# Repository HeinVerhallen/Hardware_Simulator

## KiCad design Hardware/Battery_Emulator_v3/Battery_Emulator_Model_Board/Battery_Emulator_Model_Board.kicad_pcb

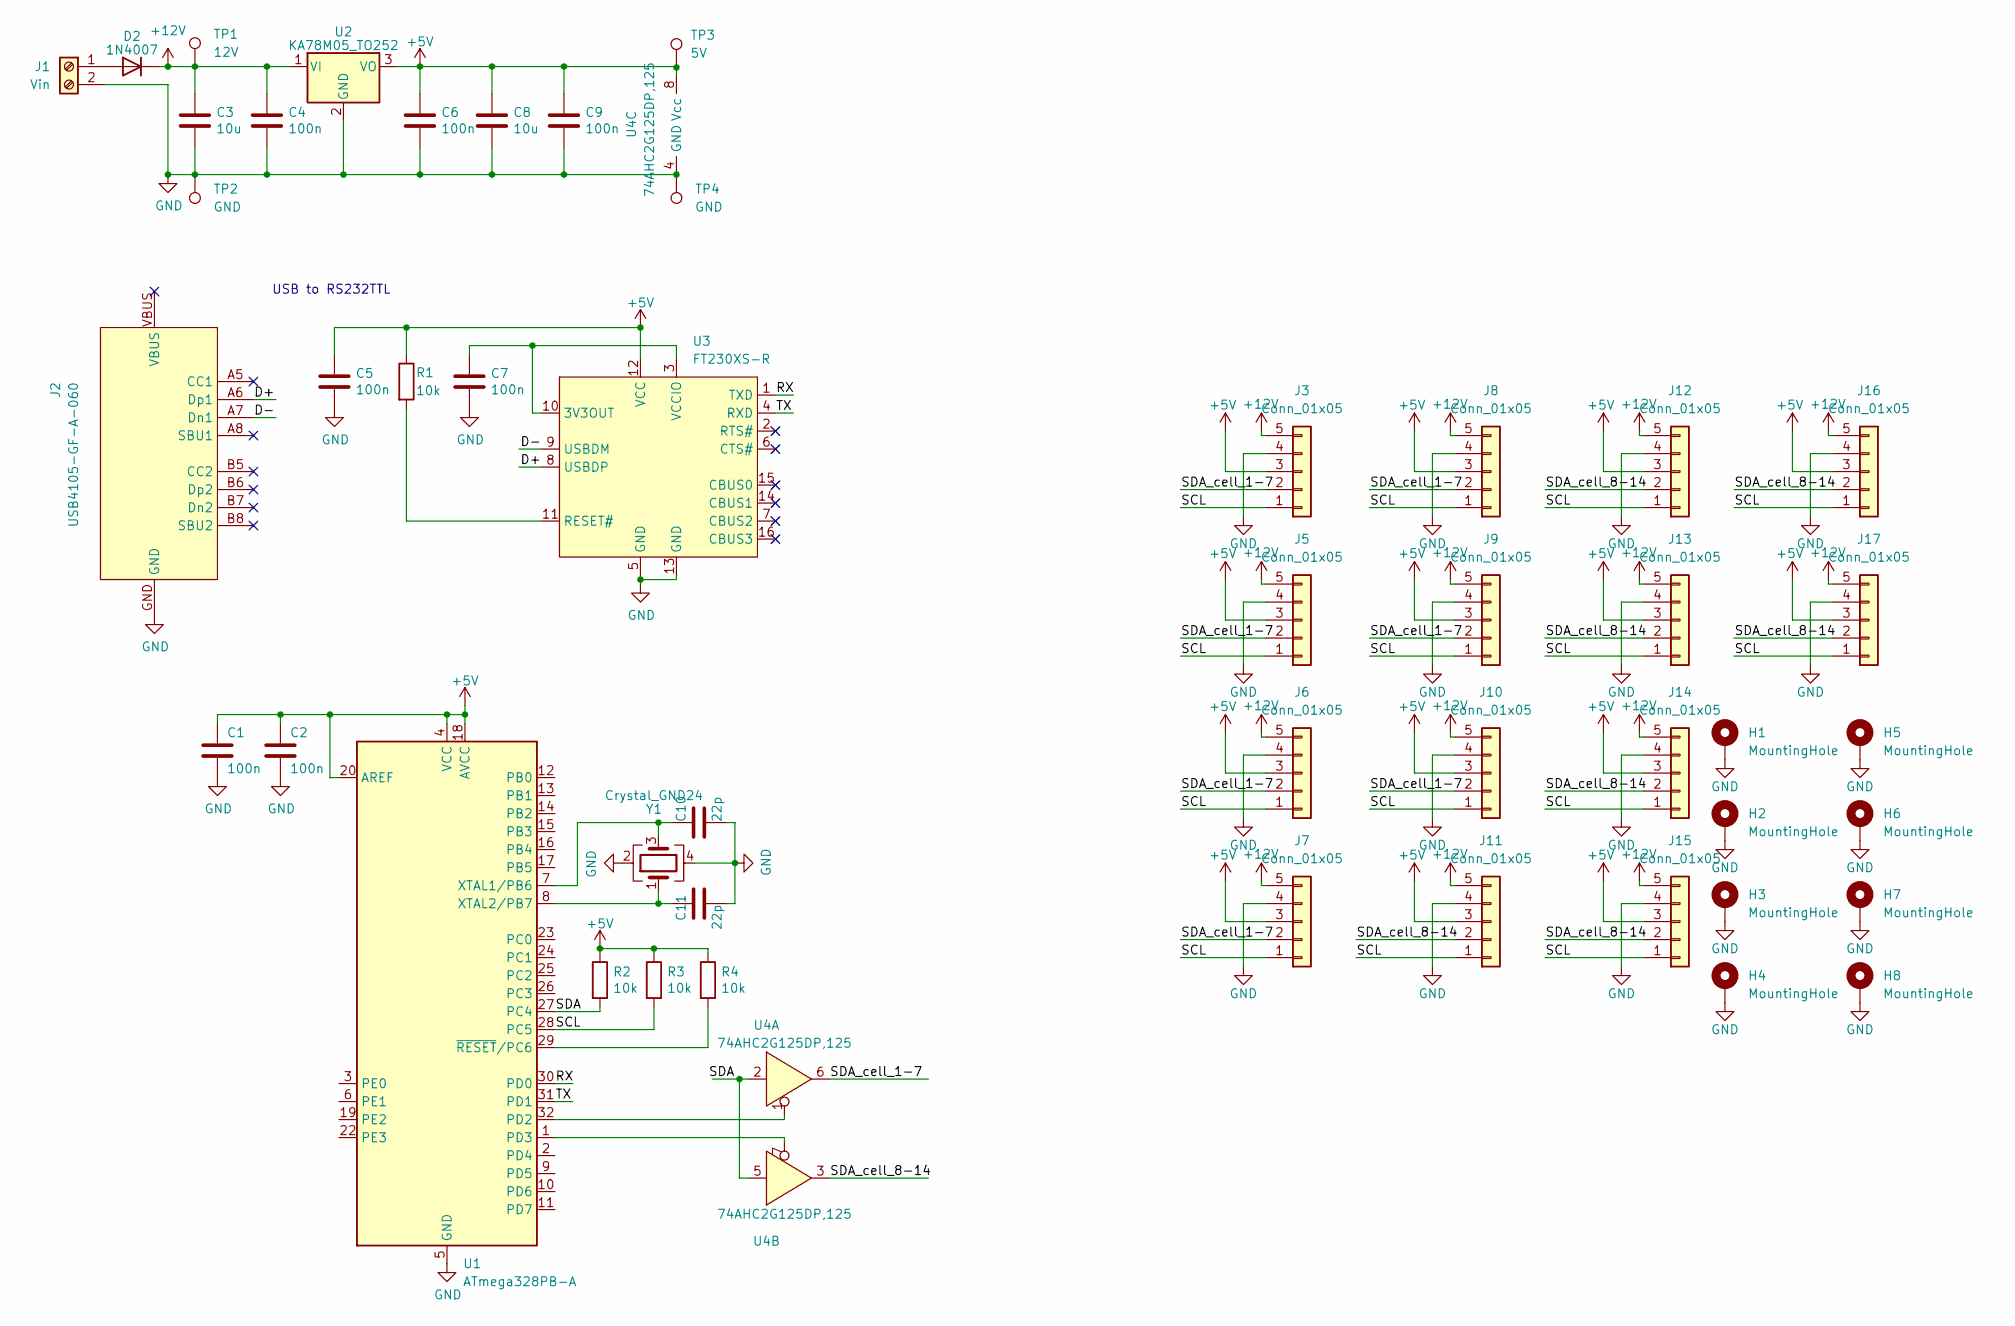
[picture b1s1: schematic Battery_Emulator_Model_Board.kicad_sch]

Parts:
C1, C2, C4, C5, C6, C7, C9: 100n; C_0805_2012Metric
C3, C8: 10u; C_0805_2012Metric
C10, C11: 22p; C_0805_2012Metric
D2: 1N4007; D_DO-41_SOD81_P2.54mm_Vertical_KathodeUp
H1, H2, H3, H4, H5, H6, H7, H8: MountingHole; MountingHole_3.2mm_M3_Pad_Via
J1: Vin; TerminalBlock_Phoenix_MKDS-1,5-2-5.08_1x02_P5.08mm_Horizont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
J2: USB4105-GF-A-060; GCT_USB4105-GF-A-060
J3, J5, J6, J7, J8, J9, J10, J11, J12, J13, J14, J15, J16, J17: Conn_01x05; PinSocket_1x05_P2.54mm_Horizontal
R1, R2, R3, R4: 10k; R_0805_2012Metric
TP1: 12V; TestPoint_Pad_D2.5mm
TP2, TP4: GND; TestPoint_Pad_D2.5mm
TP3: 5V; TestPoint_Pad_D2.5mm
U1: ATmega328PB-A; TQFP-32_7x7mm_P0.8mm
U2: KA78M05_TO252; TO-252-2
U3: FT230XS-R; SSOP-16_3.9x4.9mm_P0.635mm
U4: 74AHC2G125DP,125; TSSOP-8_3x3mm_P0.65mm
Y1: Crystal_GND24; Crystal_SMD_3225-4Pin_3.2x2.5mm

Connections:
+5V: C1.1, C2.1, C5.1, C6.1, C8.1, C9.1, J3.3, J5.3, J6.3, J7.3, J8.3, J9.3, J10.3, J11.3, J12.3, J13.3, J14.3, J15.3, J16.3, J17.3, R1.1, R2.1, R3.1, R4.1, TP3.1, U1.4 (VCC), U1.18 (AVCC), U1.20 (AREF), U2.3 (VO), U3.12 (VCC), U4.8 (Vcc)
+12V: C3.1, C4.1, D2.1 (K), J3.5, J5.5, J6.5, J7.5, J8.5, J9.5, J10.5, J11.5, J12.5, J13.5, J14.5, J15.5, J16.5, J17.5, TP1.1, U2.1 (VI)
/D+: J2.A6 (Dp1), U3.8 (USBDP)
/D-: J2.A7 (Dn1), U3.9 (USBDM)
/RX: U1.30 (PD0), U3.1 (TXD)
/SCL: J3.1, J5.1, J6.1, J7.1, J8.1, J9.1, J10.1, J11.1, J12.1, J13.1, J14.1, J15.1, J16.1, J17.1, R3.2, U1.28 (PC5)
/SDA: R2.2, U1.27 (PC4), U4.2, U4.5
/SDA_cell_1-7: J3.2, J5.2, J6.2, J7.2, J8.2, J9.2, J10.2, U4.6
/SDA_cell_8-14: J11.2, J12.2, J13.2, J14.2, J15.2, J16.2, J17.2, U4.3
/TX: U1.31 (PD1), U3.4 (RXD)
GND: C1.2, C2.2, C3.2, C4.2, C5.2, C6.2, C7.2, C8.2, C9.2, C10.2, C11.2, H1.1, H2.1, H3.1, H4.1, H5.1, H6.1, H7.1, H8.1, J1.2, J2.GND, J3.4, J5.4, J6.4, J7.4, J8.4, J9.4, J10.4, J11.4, J12.4, J13.4, J14.4, J15.4, J16.4, J17.4, TP2.1, TP4.1, U1.5 (GND), U1.21 (GND), U2.2 (GND), U3.5 (GND), U3.13 (GND), U4.4 (GND), Y1.2, Y1.4
unnamed: D2.2 (A), J1.1
unnamed: U1.32 (PD2), U4.1
unnamed: U1.1 (PD3), U4.7
unnamed: C10.1, U1.7 (XTAL1/PB6), Y1.3
unnamed: C11.1, U1.8 (XTAL2/PB7), Y1.1
unnamed: R4.2, U1.29 (~RESET/PC6)
unnamed: C7.1, U3.3 (VCCIO), U3.10 (3V3OUT)
unnamed: R1.2, U3.11 (RESET#)

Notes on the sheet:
USB to RS232TTL

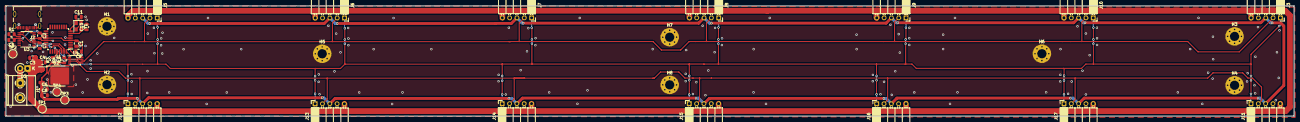
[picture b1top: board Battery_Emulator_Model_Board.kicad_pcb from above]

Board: 2 copper layers, 446.7 x 38.2 mm, 49 parts (0 on the bottom side), 19 nets.

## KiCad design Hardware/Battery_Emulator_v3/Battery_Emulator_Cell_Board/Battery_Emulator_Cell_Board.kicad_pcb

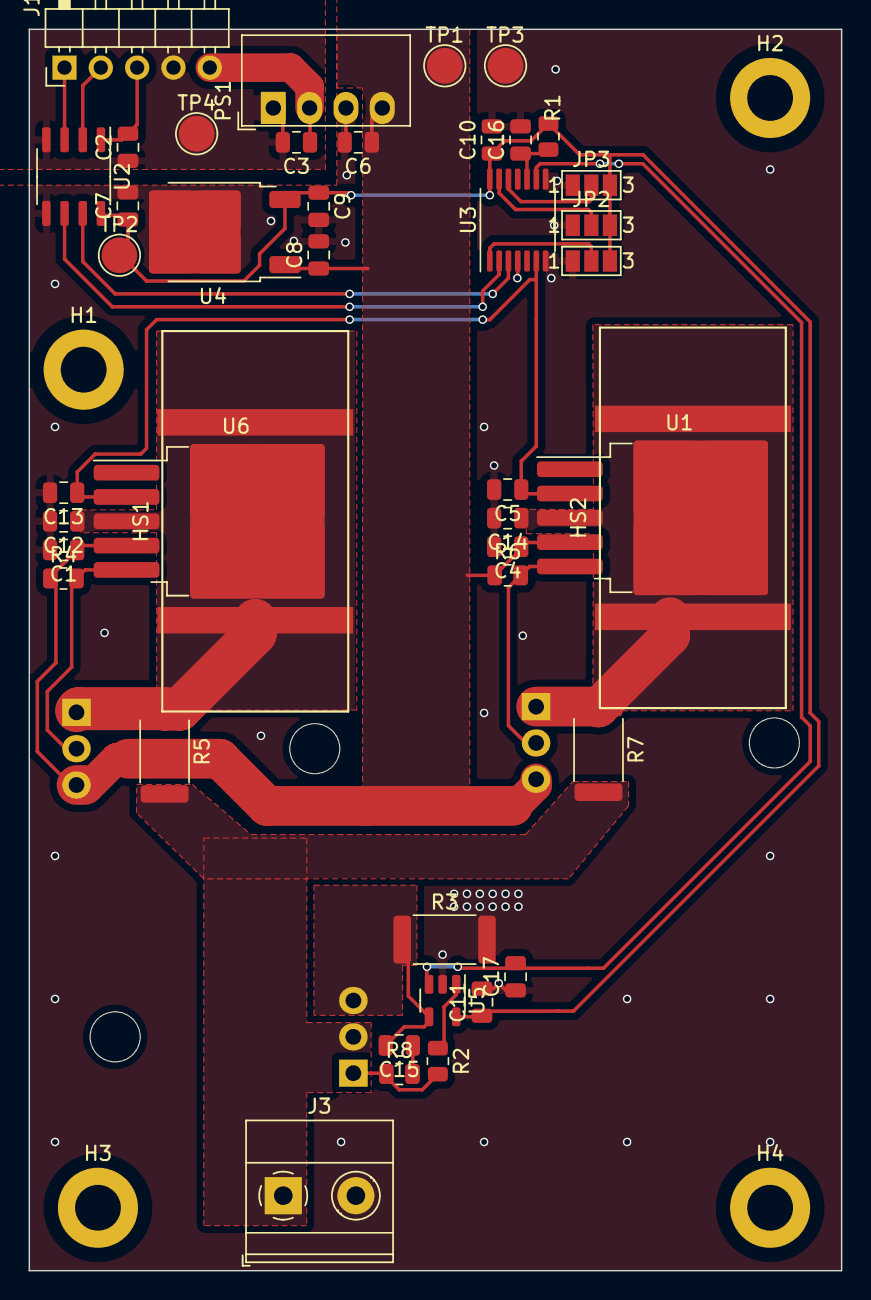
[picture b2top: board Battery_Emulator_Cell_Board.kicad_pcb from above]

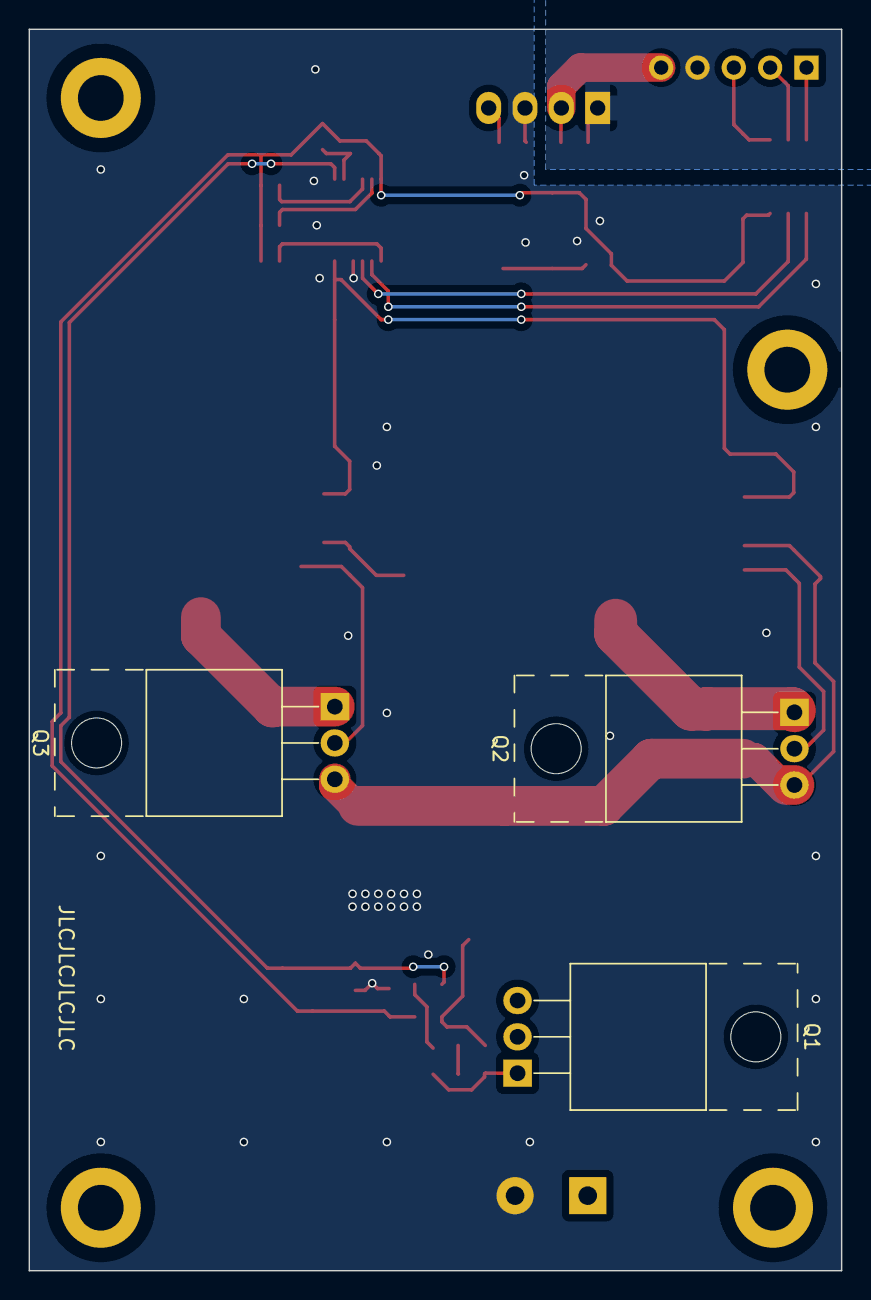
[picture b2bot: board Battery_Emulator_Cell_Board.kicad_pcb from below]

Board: 2 copper layers, 56.8 x 86.8 mm, 50 parts (3 on the bottom side), 25 nets.

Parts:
C1, C4: 1u; C_0805_2012Metric
C2, C7, C8, C9, C10, C11, C16: 100n; C_0805_2012Metric
C3, C6: 10u; C_0805_2012Metric
C5, C13: 1n; C_0805_2012Metric
C12, C14: 2u2; C_0805_2012Metric
C15: 330n; C_0805_2012Metric
C17: 10n; C_0805_2012Metric
H1, H2, H3, H4: MountingHole; MountingHole_3.2mm_M3_DIN965_Pad
HS1, HS2: Heatsink_Pad_2Pin; Heatsink_AAVID_573300D00010G_TO-263
J1: Conn_01x05; PinHeader_1x05_P2.54mm_Horizontal
J3: Cell1_Vout; TerminalBlock_Phoenix_MKDS-1,5-2-5.08_1x02_P5.08mm_Horizont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
JP1, JP2, JP3: Jumper; SolderJumper-3_P1.3mm_Open_Pad1.0x1.5mm_NumberLabels
PS1: MEE1S1209SC; Converter_DCDC_Murata_MEE1SxxxxSC_THT
Q1: IRFB7545PBF; TO-220-3_Horizontal_TabUp
Q2, Q3: MJE2955T; TO-220-3_Horizontal_TabUp
R1: 780k; R_0805_2012Metric
R2: 10k; R_0805_2012Metric
R3: 0.5m; R_2512_6332Metric
R4, R6: 47; R_0805_2012Metric
R5, R7: 20m; R_2512_6332Metric
R8: 56; R_0805_2012Metric
TP1: 9V_ISO; TestPoint_Pad_D2.5mm
TP2: 5V_ISO; TestPoint_Pad_D2.5mm
TP3: GND_ISO; TestPoint_Pad_D2.5mm
TP4: GND; TestPoint_Pad_D2.5mm
U1, U6: LT3080xQ; TO-263-5_TabPin3
U2: ISO1640BDR; SO-8_3.9x4.9mm_P1.27mm
U3: MCP4651T-103E_ST; TSSOP-14_4.4x5mm_P0.65mm
U4: KA78M05_TO252; TO-252-2
U5: MCP6001UT-I/OT; SOT-23-5

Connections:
/+5V: C2.2, J1.3, U2.1 (VCC1)
/+5V_ISO: C7.1, C9.1, C10.1, C11.1, JP1.3 (B), JP2.3 (B), JP3.3 (B), R1.1, TP2.1, U2.8 (VCC2), U3.14 (VDD), U4.3 (VO), U5.5 (Vdd)
/+9V_ISO: C1.1, C4.1, C6.1, C8.1, PS1.4 (+Vout), Q2.3 (E), Q3.3 (E), R4.1, R6.1, TP1.1, U1.4 (VCONTROL), U4.1 (VI), U6.4 (VCONTROL)
/+12V: C3.1, J1.5, PS1.2 (+Vin)
/A0: JP1.2 (C), U3.1 (HVC/A0)
/A1: JP2.2 (C), U3.13 (A1)
/A2: JP3.2 (C), U3.12 (A2)
/GND: C2.1, C3.2, J1.4, PS1.1 (-Vin), TP4.1, U2.4 (GND1)
/GND_ISO: C1.2, C4.2, C5.2, C6.2, C7.2, C8.2, C9.2, C10.2, C11.2, C12.2, C13.2, C14.2, C16.2, C17.1, J3.2, JP1.1 (A), JP2.1 (A), JP3.1 (A), PS1.3 (-Vout), R3.2, TP3.1, U2.5 (GND2), U3.4 (VSS), U3.7 (P1A), U3.8 (P0A), U4.2 (GND), U5.2 (Vss)
/I_sense: C15.2, Q1.3, R3.1, U5.4 (-)
/OUT1_ISO: C14.1, HS2.1, Q3.1 (C), R7.1, U1.3 (OUT)
/OUT2_ISO: C12.1, HS1.1, Q2.1 (C), R5.1, U6.3 (OUT)
/SCL: J1.1, U2.3 (SCL1)
/SCL_ISO: U2.6 (SCL2), U3.2 (SCL)
/SDA: J1.2, U2.2 (SDA1)
/SDA_ISO: U2.7 (SDA2), U3.3 (SDA)
unnamed: C15.1, R8.2
unnamed: J3.1, Q1.2, R5.2, R7.2
unnamed: Q1.1, R2.2, R8.1
unnamed: Q2.2 (B), R4.2, U6.5 (IN)
unnamed: Q3.2 (B), R6.2, U1.5 (IN)
unnamed: R2.1, U5.1
unnamed: C5.1, C13.1, U1.2 (SET), U3.6 (P1W), U6.2 (SET)
unnamed: C16.1, R1.2, U3.10 (P0B)
unnamed: C17.2, U3.9 (P0W), U5.3 (+)

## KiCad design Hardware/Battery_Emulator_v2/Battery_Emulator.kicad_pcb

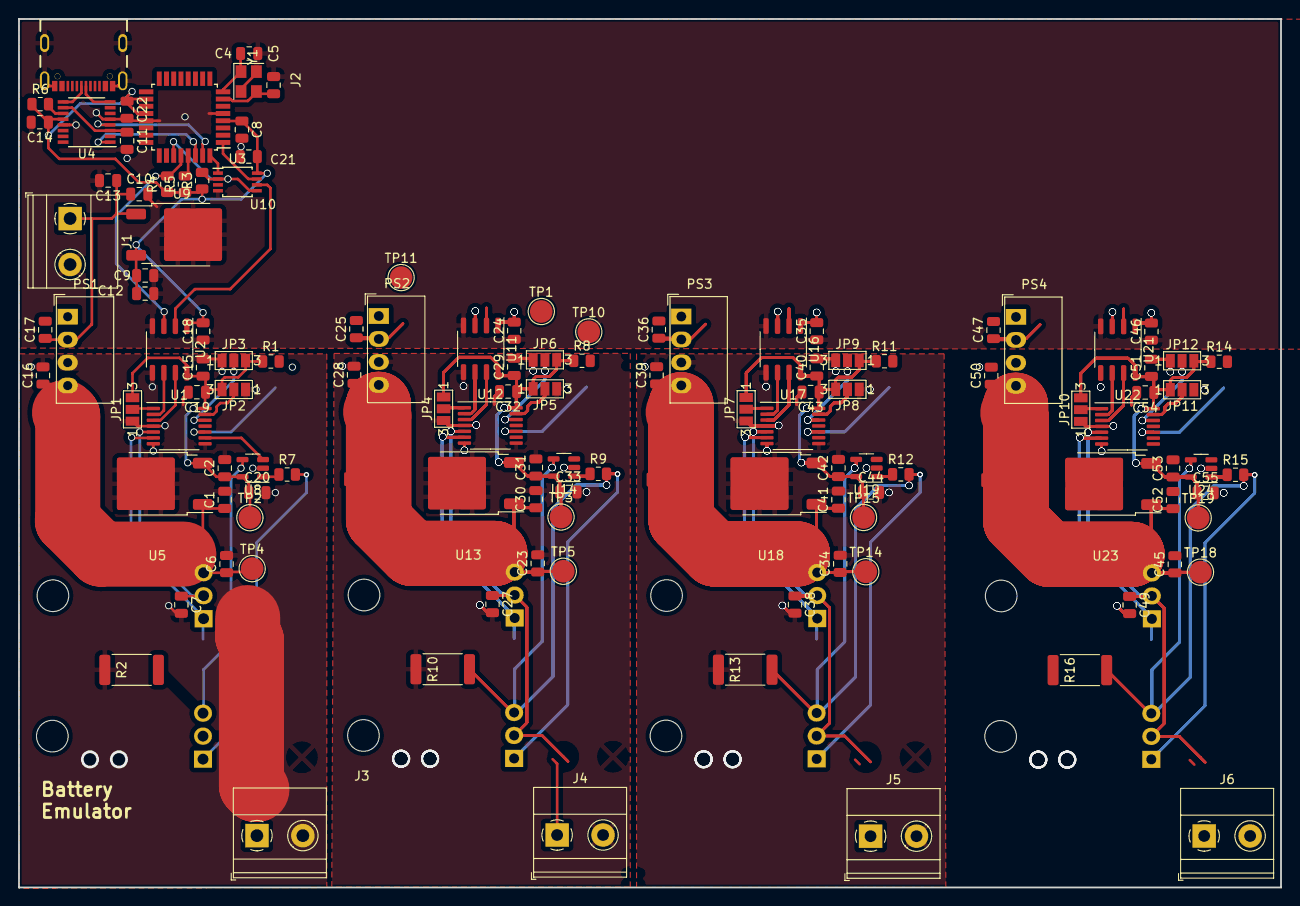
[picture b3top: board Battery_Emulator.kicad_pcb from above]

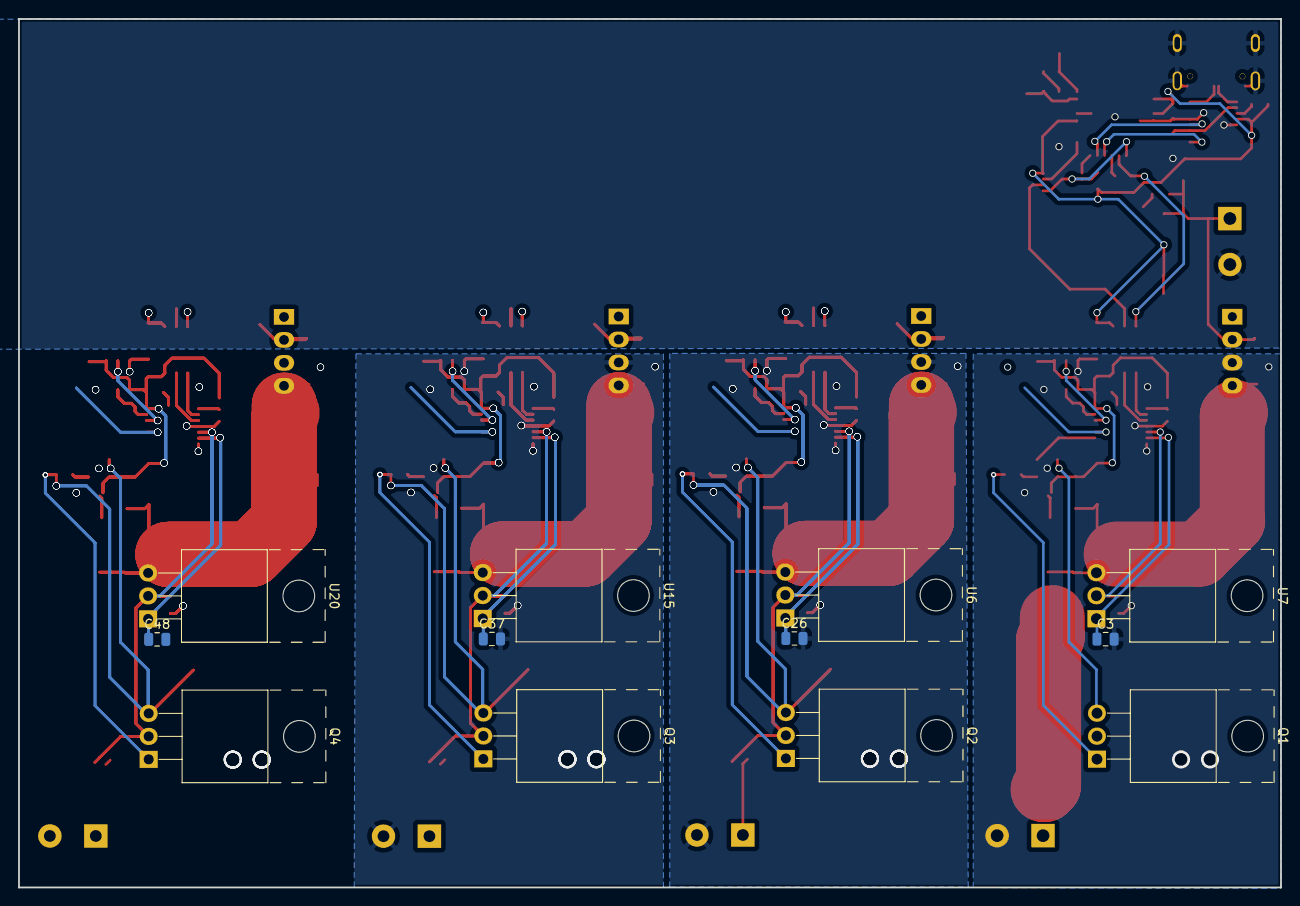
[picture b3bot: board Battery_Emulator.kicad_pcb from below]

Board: 2 copper layers, 139.5 x 96.0 mm, 133 parts (12 on the bottom side), 80 nets.

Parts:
C1, C2, C3, C6, C7, C8, C9, C10, C11, C14, C15, C18, C19, C20, C21, C22, C23, C24, C26, C27, C29, C30, C31, C32, C33, C34, C35, C37, C38, C40, C41, C42, C43, C44, C45, C46, C48, C49, C51, C52, C53, C54, C55: 100n; C_0805_2012Metric
C4, C5: 22p; C_0805_2012Metric
C12, C13, C16, C17, C25, C28, C36, C39, C47, C50: 10u; C_0805_2012Metric
J1: Vin; TerminalBlock_Phoenix_MKDS-1,5-2-5.08_1x02_P5.08mm_Horizont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
J2: USB4105-GF-A-060; GCT_USB4105-GF-A-060
J3: Cell1_Vout; TerminalBlock_Phoenix_MKDS-1,5-2-5.08_1x02_P5.08mm_Horizont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
J4: Cell2_Vout; TerminalBlock_Phoenix_MKDS-1,5-2-5.08_1x02_P5.08mm_Horizont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
J5: Cell3_Vout; TerminalBlock_Phoenix_MKDS-1,5-2-5.08_1x02_P5.08mm_Horizont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
J6: Cell4_Vout; TerminalBlock_Phoenix_MKDS-1,5-2-5.08_1x02_P5.08mm_Horizont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
JP1, JP2, JP3, JP4, JP5, JP6, JP7, JP8, JP9, JP10, JP11, JP12: Jumper; SolderJumper-3_P1.3mm_Open_Pad1.0x1.5mm_NumberLabels
PS1, PS2, PS3, PS4: MEE1S1209SC; Converter_DCDC_Murata_MEE1SxxxxSC_THT
Q1, Q2, Q3, Q4: IRFB7545PBF; TO-220-3_Horizontal_TabUp
R1, R8, R11, R14: 780k; R_0805_2012Metric
R2, R10, R13, R16: 0.5m; R_2512_6332Metric
R3, R4, R5, R6: 10k; R_0805_2012Metric
R7, R9, R12, R15: 47; R_0805_2012Metric
TP1: 5V; TestPoint_Pad_D2.5mm
TP2, TP3, TP15, TP19: 5V_ISO; TestPoint_Pad_D2.5mm
TP4, TP5, TP14, TP18: 9V_ISO; TestPoint_Pad_D2.5mm
TP10: GND; TestPoint_Pad_D2.5mm
TP11: 12V; TestPoint_Pad_D2.5mm
U1, U12, U17, U22: MCP4651T-103E_ST; TSSOP-14_4.4x5mm_P0.65mm
U2, U11, U16, U21: ISO1640BDR; SO-8_3.9x4.9mm_P1.27mm
U3: 74AHC2G125DP,125; TSSOP-8_3x3mm_P0.65mm
U4: FT230XS-R; SSOP-16_3.9x4.9mm_P0.635mm
U5, U9, U13, U18, U23: KA78M05_TO252; TO-252-2
U6, U7, U15, U20: LM317_TO-220; TO-220-3_Horizontal_TabUp
U8, U14, U19, U24: MCP6001UT-I/OT; SOT-23-5
U10: ATmega328PB-A; TQFP-32_7x7mm_P0.8mm
Y1: Crystal_GND24; Crystal_SMD_3225-4Pin_3.2x2.5mm

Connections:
+5V: C8.1, C9.1, C12.1, C14.1, C18.2, C21.1, C22.1, C24.2, C35.2, C46.2, R3.1, R4.1, R5.1, R6.1, TP1.1, U2.1 (VCC1), U3.8 (Vcc), U4.12 (VCC), U9.3 (VO), U10.4 (VCC), U10.18 (AVCC), U10.20 (AREF), U11.1 (VCC1), U16.1 (VCC1), U21.1 (VCC1)
+12V: C10.1, C13.1, C17.1, C25.1, C36.1, C47.1, J1.1, PS1.2 (+Vin), PS2.2 (+Vin), PS3.2 (+Vin), PS4.2 (+Vin), TP11.1, U9.1 (VI)
/Cell_1/+5V_ISO: C2.1, C15.1, C19.1, C20.1, JP1.3 (B), JP2.3 (B), JP3.3 (B), R1.1, TP2.1, U1.14 (VDD), U2.8 (VCC2), U5.3 (VO), U8.5 (Vdd)
/Cell_1/+9V_ISO: C1.1, C6.1, C16.1, PS1.4 (+Vout), TP4.1, U5.1 (VI), U7.3 (VI)
/Cell_1/A0: JP1.2 (C), U1.1 (HVC/A0)
/Cell_1/A1: JP2.2 (C), U1.13 (A1)
/Cell_1/A2: JP3.2 (C), U1.12 (A2)
/Cell_1/GND_ISO: C1.2, C2.2, C3.2, C6.2, C7.2, C15.2, C16.2, C19.2, C20.2, J3.2, JP1.1 (A), JP2.1 (A), JP3.1 (A), PS1.3 (-Vout), R2.2, U1.4 (VSS), U1.7 (P1A), U1.8 (P0A), U2.5 (GND2), U5.2 (GND), U8.2 (Vss)
/Cell_1/SCL_ISO: U1.2 (SCL), U2.6 (SCL2)
/Cell_1/SDA_ISO: U1.3 (SDA), U2.7 (SDA2)
/Cell_2/+5V_ISO: C29.1, C31.1, C32.1, C33.1, JP4.3 (B), JP5.3 (B), JP6.3 (B), R8.1, TP3.1, U11.8 (VCC2), U12.14 (VDD), U13.3 (VO), U14.5 (Vdd)
/Cell_2/+9V_ISO: C23.1, C28.1, C30.1, PS2.4 (+Vout), TP5.1, U6.3 (VI), U13.1 (VI)
/Cell_2/A0: JP4.2 (C), U12.1 (HVC/A0)
/Cell_2/A1: JP5.2 (C), U12.13 (A1)
/Cell_2/A2: JP6.2 (C), U12.12 (A2)
/Cell_2/COUT+: C27.1, J4.1, Q2.2, U6.2 (VO), U12.5 (P1B)
/Cell_2/GND_ISO: C23.2, C26.2, C27.2, C28.2, C29.2, C30.2, C31.2, C32.2, C33.2, J4.2, JP4.1 (A), JP5.1 (A), JP6.1 (A), PS2.3 (-Vout), R10.2, U11.5 (GND2), U12.4 (VSS), U12.7 (P1A), U12.8 (P0A), U13.2 (GND), U14.2 (Vss)
/Cell_2/SCL_ISO: U11.6 (SCL2), U12.2 (SCL)
/Cell_2/SDA_ISO: U11.7 (SDA2), U12.3 (SDA)
/Cell_3/+5V_ISO: C40.1, C42.1, C43.1, C44.1, JP7.3 (B), JP8.3 (B), JP9.3 (B), R11.1, TP15.1, U16.8 (VCC2), U17.14 (VDD), U18.3 (VO), U19.5 (Vdd)
/Cell_3/+9V_ISO: C34.1, C39.1, C41.1, PS3.4 (+Vout), TP14.1, U15.3 (VI), U18.1 (VI)
/Cell_3/A0: JP7.2 (C), U17.1 (HVC/A0)
/Cell_3/A1: JP8.2 (C), U17.13 (A1)
/Cell_3/A2: JP9.2 (C), U17.12 (A2)
/Cell_3/COUT+: C38.1, J5.1, Q3.2, U15.2 (VO), U17.5 (P1B)
/Cell_3/GND_ISO: C34.2, C37.2, C38.2, C39.2, C40.2, C41.2, C42.2, C43.2, C44.2, J5.2, JP7.1 (A), JP8.1 (A), JP9.1 (A), PS3.3 (-Vout), R13.2, U16.5 (GND2), U17.4 (VSS), U17.7 (P1A), U17.8 (P0A), U18.2 (GND), U19.2 (Vss)
/Cell_3/SCL_ISO: U16.6 (SCL2), U17.2 (SCL)
/Cell_3/SDA_ISO: U16.7 (SDA2), U17.3 (SDA)
/Cell_4/+5V_ISO: C51.1, C53.1, C54.1, C55.1, JP10.3 (B), JP11.3 (B), JP12.3 (B), R14.1, TP19.1, U21.8 (VCC2), U22.14 (VDD), U23.3 (VO), U24.5 (Vdd)
/Cell_4/+9V_ISO: C45.1, C50.1, C52.1, PS4.4 (+Vout), TP18.1, U20.3 (VI), U23.1 (VI)
/Cell_4/A0: JP10.2 (C), U22.1 (HVC/A0)
/Cell_4/A1: JP11.2 (C), U22.13 (A1)
/Cell_4/A2: JP12.2 (C), U22.12 (A2)
/Cell_4/COUT+: C49.1, J6.1, Q4.2, U20.2 (VO), U22.5 (P1B)
/Cell_4/GND_ISO: C45.2, C48.2, C49.2, C50.2, C51.2, C52.2, C53.2, C54.2, C55.2, J6.2, JP10.1 (A), JP11.1 (A), JP12.1 (A), PS4.3 (-Vout), R16.2, U21.5 (GND2), U22.4 (VSS), U22.7 (P1A), U22.8 (P0A), U23.2 (GND), U24.2 (Vss)
/Cell_4/SCL_ISO: U21.6 (SCL2), U22.2 (SCL)
/Cell_4/SDA_ISO: U21.7 (SDA2), U22.3 (SDA)
/D+: J2.A6 (Dp1), U4.8 (USBDP)
/D-: J2.A7 (Dn1), U4.9 (USBDM)
/RX: U4.1 (TXD), U10.30 (PD0)
/SCL: R4.2, U2.3 (SCL1), U10.28 (PC5), U11.3 (SCL1), U16.3 (SCL1), U21.3 (SCL1)
/SDA: R3.2, U3.2, U3.5, U10.27 (PC4)
/SDA_cell_1-7: U2.2 (SDA1), U3.6, U11.2 (SDA1), U16.2 (SDA1), U21.2 (SDA1)
/TX: U4.4 (RXD), U10.31 (PD1)
GND: C4.2, C5.2, C8.2, C9.2, C10.2, C11.2, C12.2, C13.2, C14.2, C18.1, C21.2, C22.2, C24.1, C35.1, C46.1, J1.2, J2.GND, TP10.1, U2.4 (GND1), U3.4 (GND), U4.5 (GND), U4.13 (GND), U9.2 (GND), U10.5 (GND), U10.21 (GND), U11.4 (GND1), U16.4 (GND1), U21.4 (GND1), Y1.2, Y1.4
unnamed: C17.2, PS1.1 (-Vin)
unnamed: C25.2, PS2.1 (-Vin)
unnamed: C36.2, PS3.1 (-Vin)
unnamed: C47.2, PS4.1 (-Vin)
unnamed: Q1.1, R7.2
unnamed: Q2.1, R9.2
unnamed: Q3.1, R12.2
unnamed: Q4.1, R15.2
unnamed: R7.1, U8.1
unnamed: R9.1, U14.1
unnamed: R12.1, U19.1
unnamed: R15.1, U24.1
unnamed: R1.2, U1.10 (P0B)
unnamed: U1.9 (P0W), U8.3 (+)
unnamed: C3.1, U1.6 (P1W), U7.1 (ADJ)
unnamed: C11.1, U4.3 (VCCIO), U4.10 (3V3OUT)
unnamed: R6.2, U4.11 (RESET#)
unnamed: C7.1, J3.1, Q1.2, Q1.3, R2.1, U1.5 (P1B), U7.2 (VO), U8.4 (-)
unnamed: U3.1, U10.32 (PD2)
unnamed: U3.7, U10.1 (PD3)
unnamed: C5.1, U10.7 (XTAL1/PB6), Y1.3
unnamed: C4.1, U10.8 (XTAL2/PB7), Y1.1
unnamed: R5.2, U10.29 (~RESET/PC6)
unnamed: R8.2, U12.10 (P0B)
unnamed: U12.9 (P0W), U14.3 (+)
unnamed: C26.1, U6.1 (ADJ), U12.6 (P1W)
unnamed: Q2.3, R10.1, U14.4 (-)
unnamed: C37.1, U15.1 (ADJ), U17.6 (P1W)
unnamed: R11.2, U17.10 (P0B)
unnamed: U17.9 (P0W), U19.3 (+)
unnamed: Q3.3, R13.1, U19.4 (-)
unnamed: C48.1, U20.1 (ADJ), U22.6 (P1W)
unnamed: R14.2, U22.10 (P0B)
unnamed: U22.9 (P0W), U24.3 (+)
unnamed: Q4.3, R16.1, U24.4 (-)

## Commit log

2023-09-04 Created Plan of approach Latex doc
2023-09-05 Update PoA
    Added abbreviations in main.tex
2023-09-05 Added block diagram of project description
2023-09-05 Update PoA
    Added text to project result chapter
2023-09-05 Update PoA
    Updated global project description diagram.
    Updated text in projectresult chapter.
2023-09-05 Update PoA
    updated project result
2023-09-05 Riskanalysis
2023-09-05 quality assurance
2023-09-05 Background added
2023-09-05 Updated Background
    removed align and added new lines
2023-09-05 updated QA
2023-09-05 Updates PoA
2023-09-05 Added Milestones
2023-09-05 Added cost benefit
2023-09-05 Update Background.tex
    Replaced the \\ with normal enters which doesn't change the layout.
2023-09-05 Updated Projectboundaries.tex
2023-09-05 Update PoA
    Added planning in planning chapter and made it a landscape page such that the planning fits.
    Also created a new detailed planning in excel.
2023-09-05 Update main.tex
    Updated abbreviation list
2023-09-08 Update PoA
    processed feedback we got from Ralph. Fixed requirements, added mid-term presentation in planning. Added reference to table in risk analysis. Adjusted sentence in project boundaries.
2023-09-08 Small change in cost-benefit
    Changed "you" to "the team"
2023-09-08 Added team meetings
2023-09-08 layout edit
2023-09-13 Updated project organization and risk analysis
2023-09-13 updated projectboundaries
2023-09-13 Updated Milestones
2023-09-13 Update PoA
    added new part in project result chapter.
    Made functional and non-functional requirements in excel document.
2023-09-13 Made a simple simulation of the operating principle of a DC-load
2023-09-19 Created updated broad planning
2023-09-20 Update PoA
2023-09-20 Update PoA
    Updated broad planning. Included requirements and broad planning in latex as image
2023-09-20 Cleaned up PoA
2023-09-20 Changed file structure in Documentation folder
2023-09-20 added commas, added 4th iteration in project activities
2023-09-27 Update broad planning
2023-09-27 Made pictures from battery cell diagram
2023-10-04 Created Battery Emulator Schematic
2023-10-04 DC-motor updates
2023-10-04 configured custom symbols and footprints structure
2023-10-04 deleted old kicad version files
2023-10-04 migrated the symbol library
2023-10-04 Created current sink simulation
2023-10-04 Added Cell Hierachy
2023-10-04 Added FT230XS-R
2023-10-11 Added USB-C and Crystal Components
    Symbols + Footprints
2023-10-11 Created avr-i2c-library
2023-10-11 Added ATMega and fixed isolated voltage level
    12V_ISO -> 9V_ISO
2023-10-11 Created cell_emulator code
2023-10-11 Inputted all components and values
2023-10-11 small move of a gnd
2023-10-25 Updated schematic battery emulator
    Made schematic more clear. Fixed some bugs
2023-10-25 wrote code for voltage level setting
2023-11-01 Added components to PCB and started the layout
    Also added footprints for the pots, jumpers and power connector
2023-11-01 Update PCB
    Made PCB in Kicad
2023-11-01 Update PCB design
2023-11-01 Worked on current sink simulations in order to improve stability
2023-11-01 Update PCB
    Made traces a lot larger to pass more current.
    Added resistor to gate of current sink MOSFET.
    Made the gerber files and ordered it at SMD lab.
2023-11-02 Update PCB
    Changed via hole sizes to 0.6mm so it can be made in SMD lab
2023-11-06 Added a second version of the hardware
2023-11-06 Modified the v2 pcb
2023-11-06 Update PCB
    Updated the via sizes to 0.8mm in v1
2023-11-07 PCB-update for production
2023-11-15 testplan
2023-11-15 Hardware Update
    V2 with four cells with the same layout
2023-11-15 Linear regulator simulations addidions and cleanup
2023-11-15 Hardware Update
    Made a v3 that has a model board PCB and a cell board PCB. Made both schematics and started on the layout of the model board PCB.
2023-11-22 Hardware Update
    Updated the v3 model board PCB layout.
2023-11-22 Hardware Update
    Finished the Model Board PCB
2023-11-22 added ESR resistance for stabililty
2023-11-22 Hardware update
    updated the model board pcb and the cell pcb
2023-11-22 Added new lin-reg topology. Use this LT3080-1 schematic for the design
2023-11-22 Update battery emulator v3 design
    Updated design such that its is parallel with the pins
2023-11-23 Updated mother board + cell PCB
    Made +12V trace on mother board 2mm so it can withstand 2A. Improved routing a bit. Changed pinheader to pinsocket on motherboard and pinsocket to pinheader on cell PCB. Mother board is nearly finish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
2023-11-27 Updated model board a bit after review
2023-11-29 Updated Mother board and Cell board
    Changed pinout of mother board and cell board such that the pin headers are on the top side. Finished mother board PCB and did DRC check on it.
2023-11-29 Updated Lin reg simulation to LT3080 instead of LT3080-1
2023-11-29 Hardware Update
    Added the symbols for the LT3080, and the transistor
2023-11-29 added current sink control
2023-11-29 added reverse polarity protection
2023-11-29 Update Cell emulator PCB
2023-11-29 Hardware Update
    Updated the layout of the cell board PCB
2023-11-29 added diode
2023-11-29 added current sink resistor
2023-12-06 update schematic
2023-12-06 Hardware update
    Updated the size of the model board, so that it has 65mm of space for each cell board.
2023-12-06 Hardware update
    Moved some of the ground vias
2023-12-06 Update Cell board
    Finished PCB layout design.
    Added two capacitors in schematic for stable feedback network for current sink.
2023-12-06 Generated Gerber files
    Generated gerber and drill files for mother board and cell board.
2023-12-13 Created MDD
2023-12-13 Documentation Update
    Made a structure to the MDD. Added background, introduction, and chapters
2023-12-13 Documentation update
    Added an abstract
2023-12-13 Documentation Update
    Added Boundary Conditions
2023-12-20 digital pot test
2023-12-20 Documentation update
    Added the requirements
2023-12-20 Poster/BOM
    I added info to the poster and the order forms
2023-12-20 Documentation Update
    Added figures and information for some of the chapters
2024-01-10 Update Final_Poster_Presentation.pptx
    Replaced the word model board with mother board
2024-01-10 updated test code
2024-01-16 Documentation update
    small spelling error
2024-01-16 update
    changed testing to simulation, added photos to realization
2024-01-17 Documentation update
    added different files for every subsection of first and second iteration
2024-01-17 fixed some spelling mistakes
2024-01-17 Documentation update
    Almost everything in first iteration if finished.
2024-01-17 Documentation update
    MDD layout was fixed and more info added
2024-01-17 Documentation update
    More info and structure
2024-01-17 added comments
2024-01-18 Refactor main.cpp: Remove unused variables and add test function
2024-01-23 Firmware update
    Added a second wiper write. probably wrongly?
2024-01-23 Documentation update
    Added more iinfo
2024-01-23 Documentation update
    referenced to the figures.
2024-01-23 Added some text
2024-01-24 Documentation update
    fixed some small mistakes in 2nd iteration hardware
2024-01-24 Documentation update
    Minor things
2024-01-24 added tests for new potentiometer
2024-01-25 added testing chapters
2024-01-25 wrote software explanation and testing
2024-01-25 Added text and fixed image problem
2024-01-25 Added text for the PCB design and some more
2024-01-25 Moved images to appendix and updated PCBA screenshots to pictures
2024-01-25 updated .gitignore file
2024-01-25 Updated images
2024-01-25 Documentation Update
    Added recommendation
2024-01-25 Updated remaning block diagrams to *.pdf
2024-01-25 moved graphics to seperate folder
2024-01-25 Enough for today
2024-01-25 Added the forgotten image of the PM and GM of the current sink and refered to it in the text
2024-01-25 Documentation update
    Small fixes
2024-01-25 Documentation update
    Added Conclusion and Recommendations
2024-01-30 Corrected spelling mistakes
2024-01-30 Fixed spelling mistaces
2024-01-30 Documentation Update
    Added stuff to conclusion and recommendation and fixed some spelling mistakes.
2024-01-30 Added pictures
2024-01-30 Documentation update
    fixed some spelling mistakes
2024-01-30 made layout changes and fixed warnings
2024-01-30 Documentation Update
2024-01-30 Stashed
2024-01-30 Documentation Update
    Added the test table
2024-01-30 Documentation Update
    Test plan format
2024-01-30 Documentation Update
    Added the test plan to the Apendix
2024-01-30 Code cleanup
2024-01-31 spelling
2024-01-31 grammar
2024-01-31 Documentation Update
    Some small stuff
2024-01-31 last changes
2024-01-31 Documentation Update
    Finilized the Test Plan
2024-02-01 Added test plan to appendix
2024-02-01 Fixed some minor details
2024-02-01 Added a bit more explanation
2024-02-01 Final changes from my side. Good to hand in from my side
2024-02-01 updated the recommendations
2024-02-01 Added some final comments to the code
